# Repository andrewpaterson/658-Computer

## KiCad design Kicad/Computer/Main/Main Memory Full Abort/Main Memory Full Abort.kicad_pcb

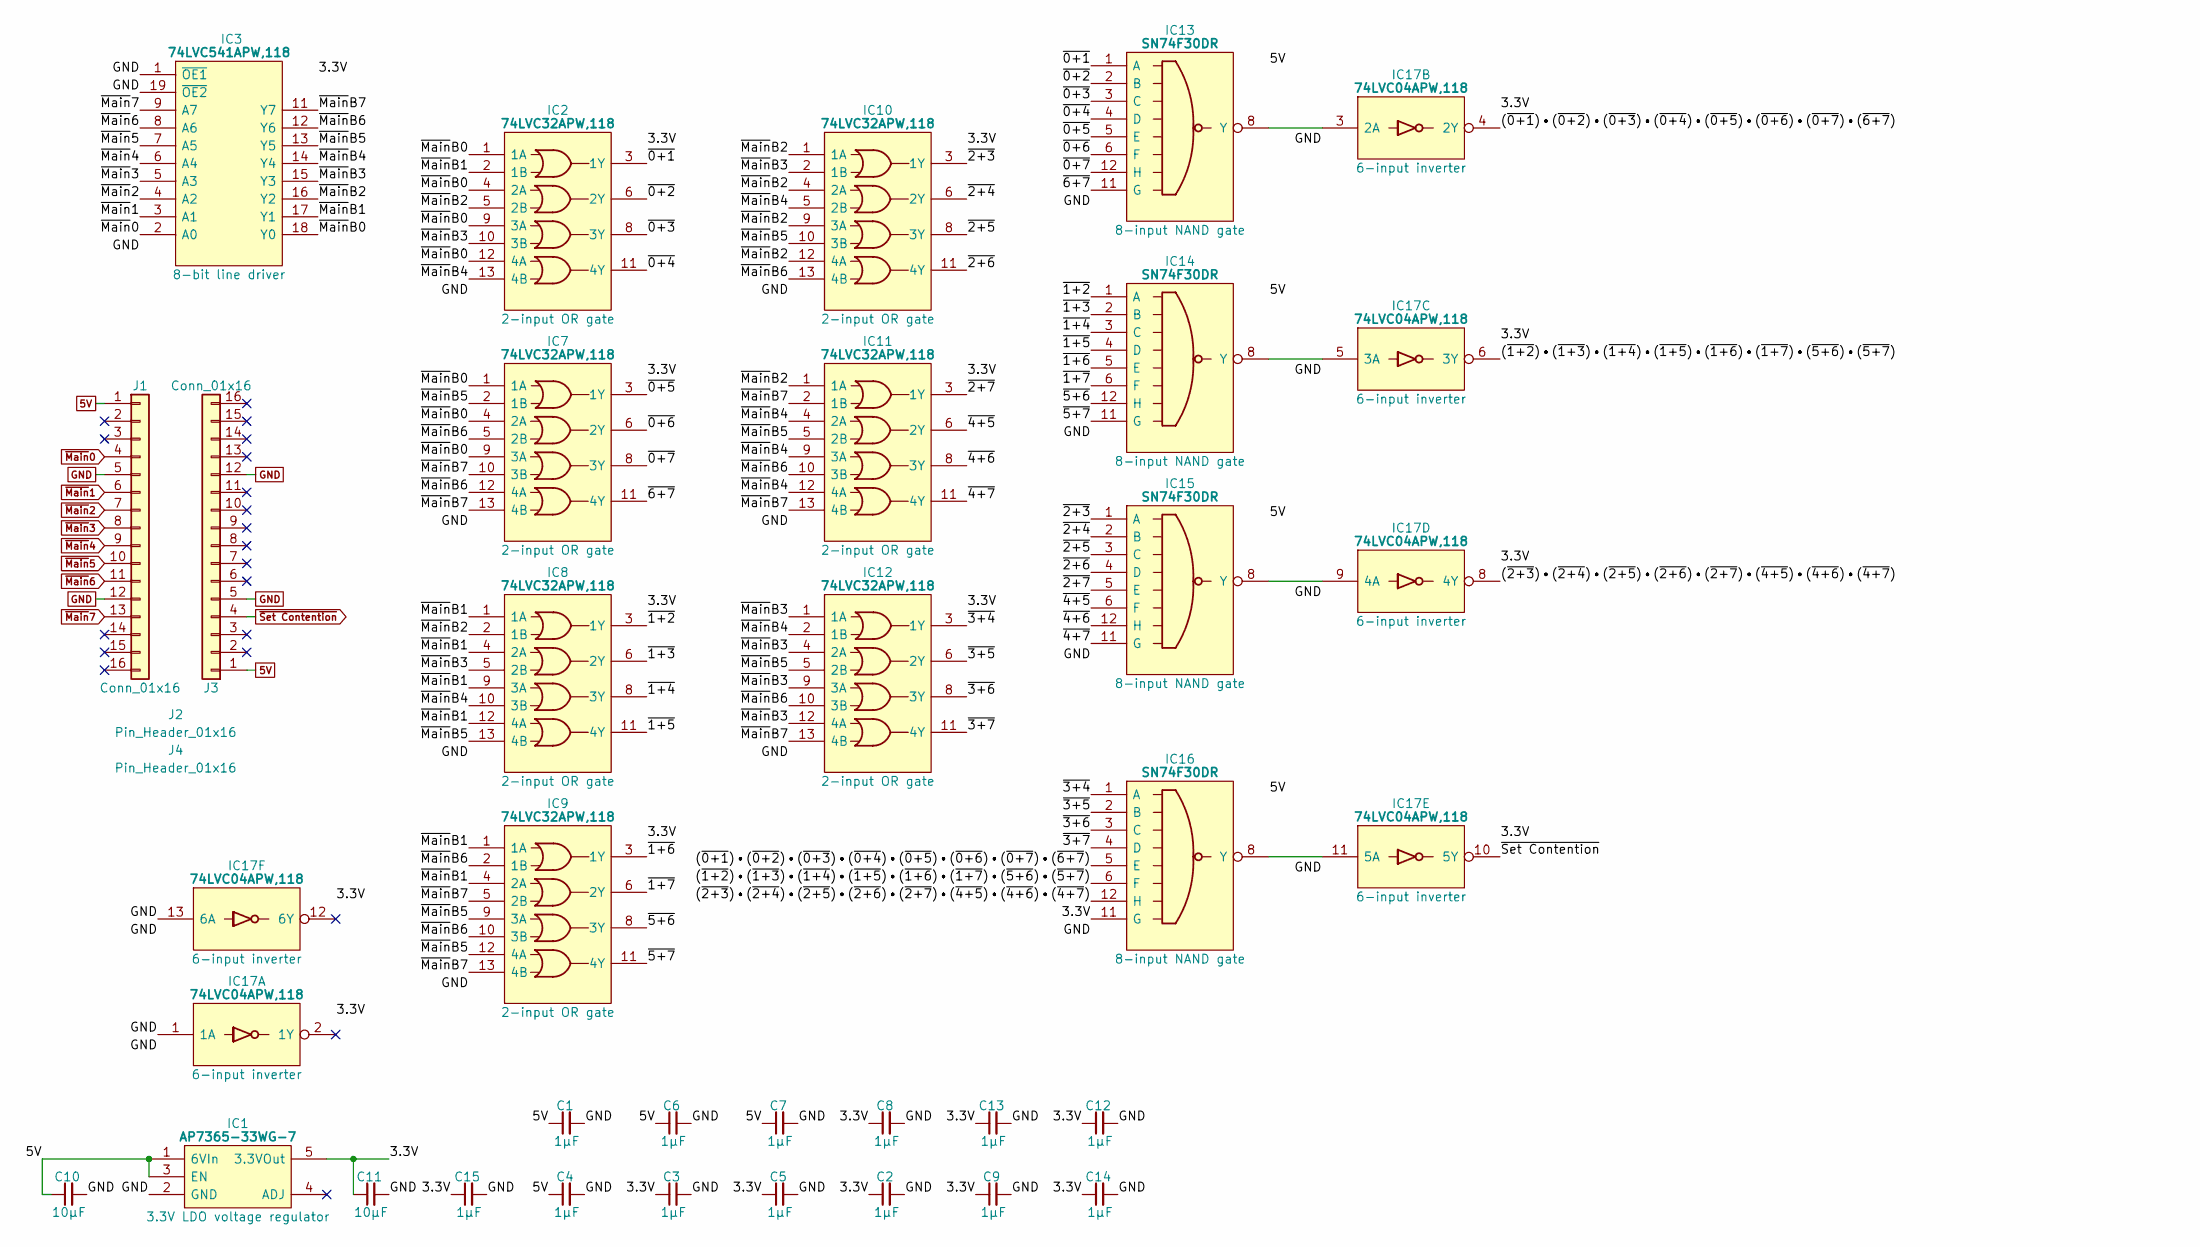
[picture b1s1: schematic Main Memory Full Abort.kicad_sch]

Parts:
C1, C2, C3, C4, C5, C6, C7, C8, C9, C12, C13, C14, C15: 1μF; C_0805
C10, C11: 10µF; C_0805
IC1: AP7365-33WG-7; SOT95P285X130-5N; Manufacturer_Part_Number AP7365-33WG-7; Mouser Part Number 621-AP7365-33WG-7
IC2, IC7, IC8, IC9, IC10, IC11, IC12: 74LVC32APW,118; SOP65P640X110-14N; Manufacturer_Part_Number 74LVC32APW,118; Mouser Part Number 771-74LVC32APW-T
IC3: 74LVC541APW,118; SOP65P640X110-20N; Mouser Part Number 771-74LVC541APW-T
IC13, IC14, IC15, IC16: SN74F30DR; SOIC127P600X175-14N; Manufacturer_Part_Number SN74F30DR; Mouser Part Number 595-SN74F30DR
IC17: 74LVC04APW,118; SOP65P640X110-14N; Manufacturer_Part_Number 74LVC04APW,118; Mouser Part Number 771-74LVC04APW-T
J1, J3: Conn_01x16; SIP_16_Pins
J2, J4: Pin_Header_01x16; PinHeader_1x16_P2.54mm_Vertical

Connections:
5V: C1.1, C4.1, C6.1, C7.1, C10.1, IC1.1 (6VIn), IC1.3 (EN), IC13.14 (5V), IC14.14 (5V), IC15.14 (5V), IC16.14 (5V), J1.1, J3.1
/3.3V: C2.1, C3.1, C5.1, C8.1, C9.1, C11.1, C12.1, C13.1, C14.1, C15.1, IC1.5 (3.3VOut), IC2.14 (3V), IC3.20 (3V), IC7.14 (3V), IC8.14 (3V), IC9.14 (3V), IC10.14 (3V), IC11.14 (3V), IC12.14 (3V), IC16.11 (G), IC17.14 (3V)
/(~0+1)•(~0+2)•(~0+3)•(~0+4)•(~0+5)•(~0+6)•(~0+7)•(~6+7): IC16.5 (E), IC17.4 (2Y)
/(~1+2)•(~1+3)•(~1+4)•(~1+5)•(~1+6)•(~1+7)•(~5+6)•(~5+7): IC16.6 (F), IC17.6 (3Y)
/(~2+3)•(~2+4)•(~2+5)•(~2+6)•(~2+7)•(~4+5)•(~4+6)•(~4+7): IC16.12 (H), IC17.8 (4Y)
/~0+1: IC2.3 (1Y), IC13.1 (A)
/~0+2: IC2.6 (2Y), IC13.2 (B)
/~0+3: IC2.8 (3Y), IC13.3 (C)
/~0+4: IC2.11 (4Y), IC13.4 (D)
/~0+5: IC7.3 (1Y), IC13.5 (E)
/~0+6: IC7.6 (2Y), IC13.6 (F)
/~0+7: IC7.8 (3Y), IC13.12 (H)
/~1+2: IC8.3 (1Y), IC14.1 (A)
/~1+3: IC8.6 (2Y), IC14.2 (B)
/~1+4: IC8.8 (3Y), IC14.3 (C)
/~1+5: IC8.11 (4Y), IC14.4 (D)
/~1+6: IC9.3 (1Y), IC14.5 (E)
/~1+7: IC9.6 (2Y), IC14.6 (F)
/~2+3: IC10.3 (1Y), IC15.1 (A)
/~2+4: IC10.6 (2Y), IC15.2 (B)
/~2+5: IC10.8 (3Y), IC15.3 (C)
/~2+6: IC10.11 (4Y), IC15.4 (D)
/~2+7: IC11.3 (1Y), IC15.5 (E)
/~3+4: IC12.3 (1Y), IC16.1 (A)
/~3+5: IC12.6 (2Y), IC16.2 (B)
/~3+6: IC12.8 (3Y), IC16.3 (C)
/~3+7: IC12.11 (4Y), IC16.4 (D)
/~4+5: IC11.6 (2Y), IC15.6 (F)
/~4+6: IC11.8 (3Y), IC15.12 (H)
/~4+7: IC11.11 (4Y), IC15.11 (G)
/~5+6: IC9.8 (3Y), IC14.12 (H)
/~5+7: IC9.11 (4Y), IC14.11 (G)
/~6+7: IC7.11 (4Y), IC13.11 (G)
/~MainB0: IC2.1 (1A), IC2.4 (2A), IC2.9 (3A), IC2.12 (4A), IC3.18 (Y0), IC7.1 (1A), IC7.4 (2A), IC7.9 (3A)
/~MainB1: IC2.2 (1B), IC3.17 (Y1), IC8.1 (1A), IC8.4 (2A), IC8.9 (3A), IC8.12 (4A), IC9.1 (1A), IC9.4 (2A)
/~MainB2: IC2.5 (2B), IC3.16 (Y2), IC8.2 (1B), IC10.1 (1A), IC10.4 (2A), IC10.9 (3A), IC10.12 (4A), IC11.1 (1A)
/~MainB3: IC2.10 (3B), IC3.15 (Y3), IC8.5 (2B), IC10.2 (1B), IC12.1 (1A), IC12.4 (2A), IC12.9 (3A), IC12.12 (4A)
/~MainB4: IC2.13 (4B), IC3.14 (Y4), IC8.10 (3B), IC10.5 (2B), IC11.4 (2A), IC11.9 (3A), IC11.12 (4A), IC12.2 (1B)
/~MainB5: IC3.13 (Y5), IC7.2 (1B), IC8.13 (4B), IC9.9 (3A), IC9.12 (4A), IC10.10 (3B), IC11.5 (2B), IC12.5 (2B)
/~MainB6: IC3.12 (Y6), IC7.5 (2B), IC7.12 (4A), IC9.2 (1B), IC9.10 (3B), IC10.13 (4B), IC11.10 (3B), IC12.10 (3B)
/~MainB7: IC3.11 (Y7), IC7.10 (3B), IC7.13 (4B), IC9.5 (2B), IC9.13 (4B), IC11.2 (1B), IC11.13 (4B), IC12.13 (4B)
GND: C1.2, C2.2, C3.2, C4.2, C5.2, C6.2, C7.2, C8.2, C9.2, C10.2, C11.2, C12.2, C13.2, C14.2, C15.2, IC1.2 (GND), IC2.7 (GND), IC3.1 (~OE1), IC3.10 (GND), IC3.19 (~OE2), IC7.7 (GND), IC8.7 (GND), IC9.7 (GND), IC10.7 (GND), IC11.7 (GND), IC12.7 (GND), IC13.7 (GND), IC14.7 (GND), IC15.7 (GND), IC16.7 (GND), IC17.1 (1A), IC17.7 (GND), IC17.13 (6A), J1.5, J1.12, J3.5, J3.12
unnamed: IC13.8 (Y), IC17.3 (2A)
unnamed: IC14.8 (Y), IC17.5 (3A)
unnamed: IC15.8 (Y), IC17.9 (4A)
unnamed: IC16.8 (Y), IC17.11 (5A)
~Main0: IC3.2 (A0), J1.4
~Main1: IC3.3 (A1), J1.6
~Main2: IC3.4 (A2), J1.7
~Main3: IC3.5 (A3), J1.8
~Main4: IC3.6 (A4), J1.9
~Main5: IC3.7 (A5), J1.10
~Main6: IC3.8 (A6), J1.11
~Main7: IC3.9 (A7), J1.13
~Set Contention: IC17.10 (5Y), J3.4

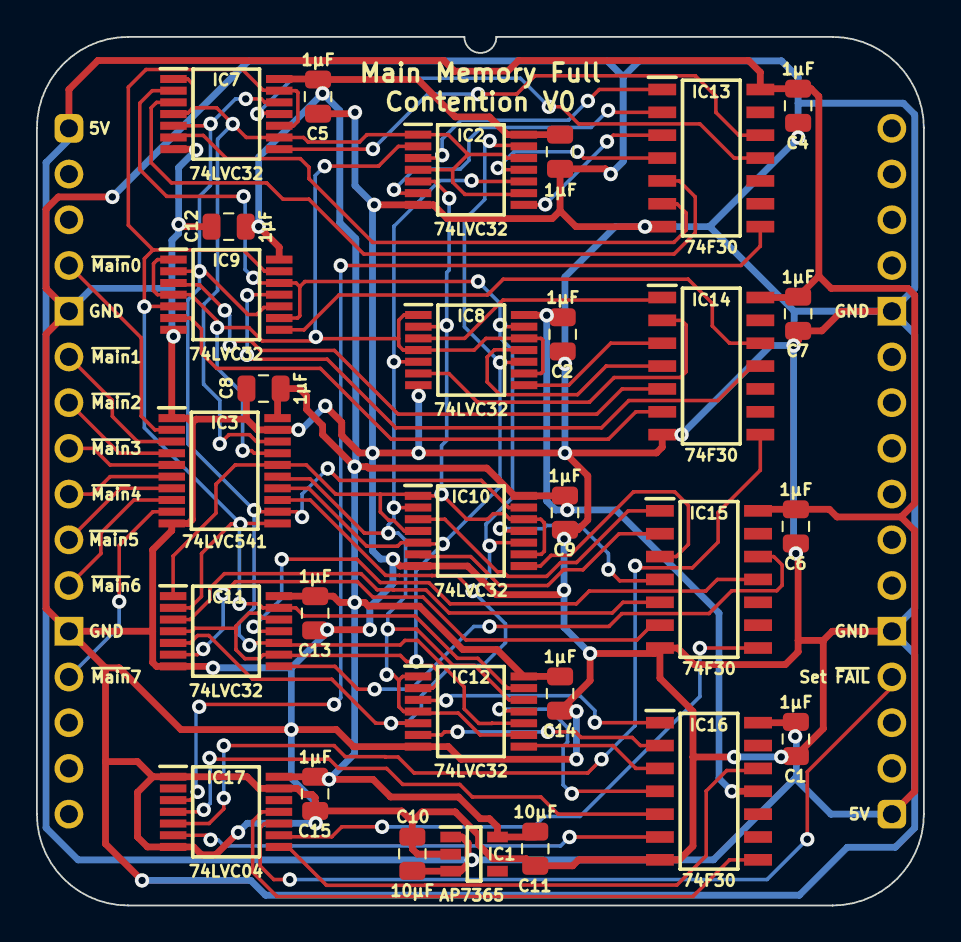
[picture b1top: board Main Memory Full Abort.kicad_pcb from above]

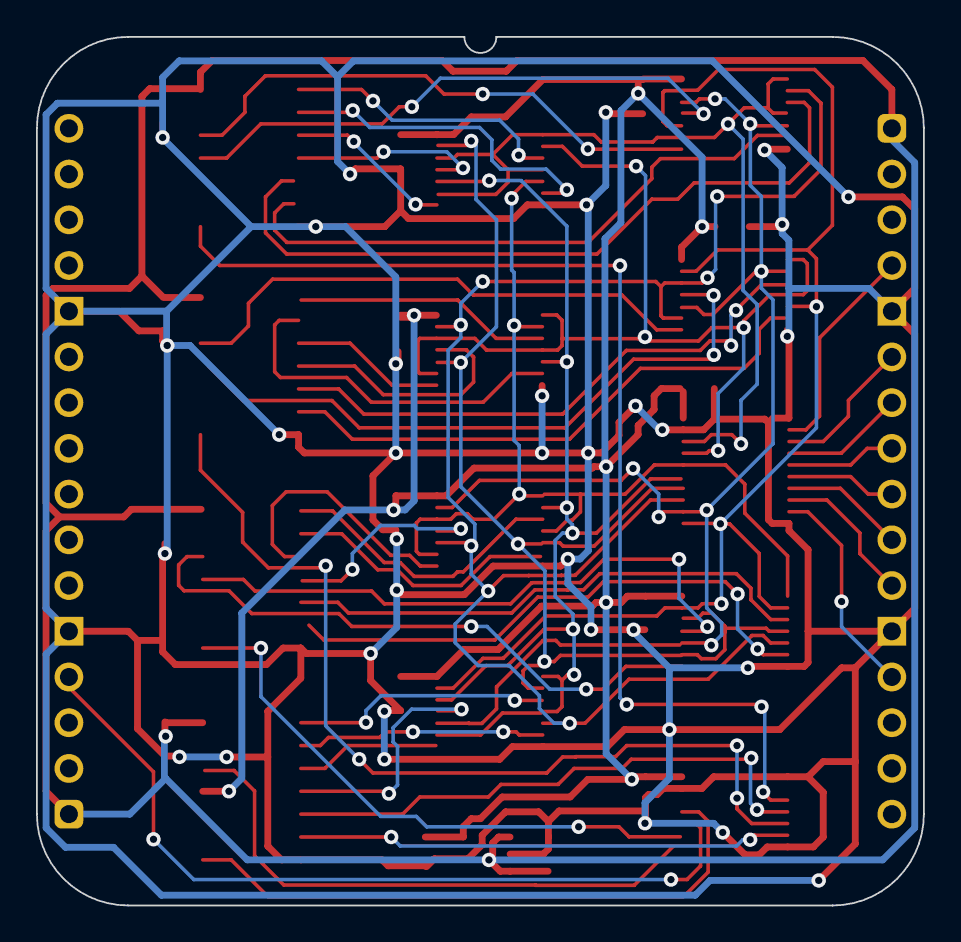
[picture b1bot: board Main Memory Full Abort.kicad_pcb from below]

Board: 2 copper layers, 49.3 x 48.3 mm, 33 parts (2 on the bottom side), 55 nets.

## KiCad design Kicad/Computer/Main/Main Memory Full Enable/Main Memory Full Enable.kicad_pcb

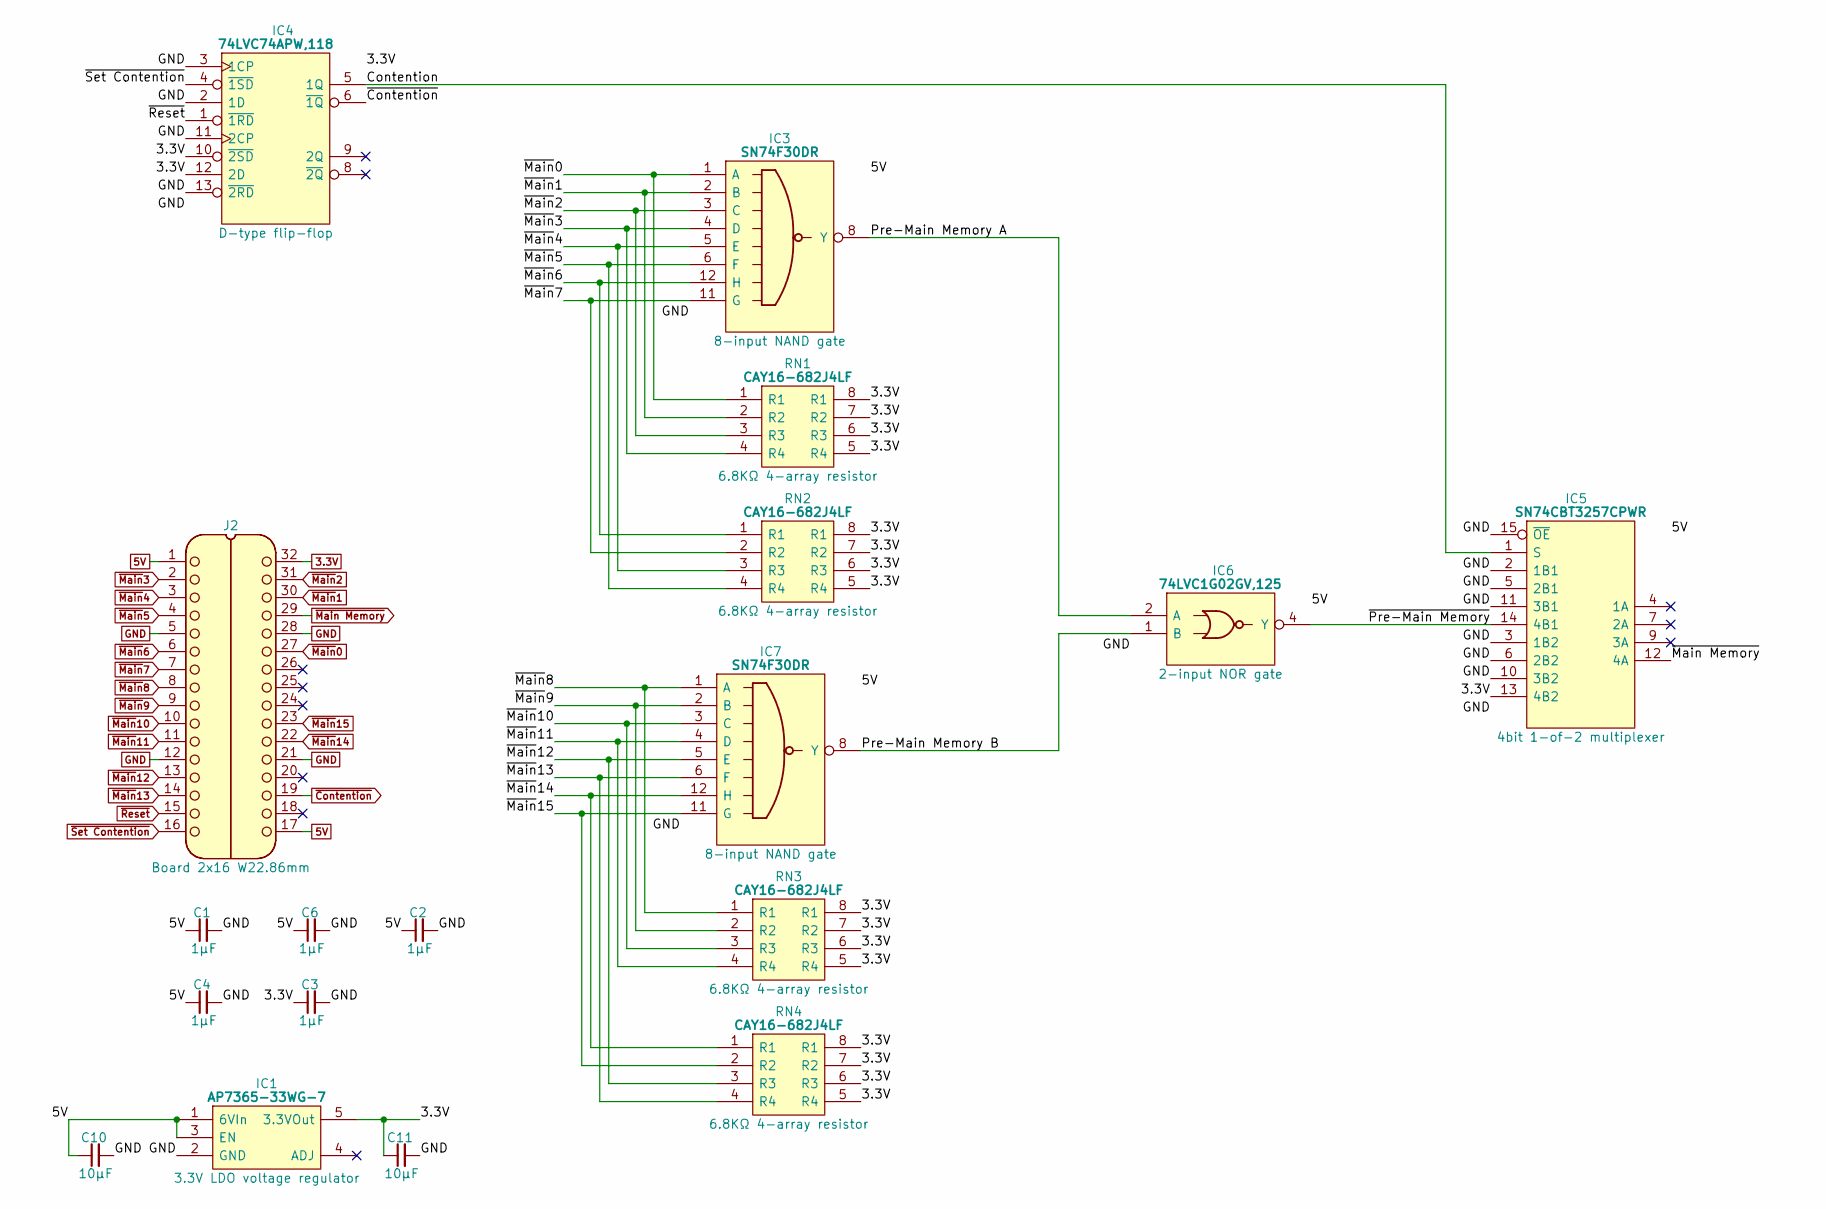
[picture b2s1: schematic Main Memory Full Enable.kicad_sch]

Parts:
C1, C2, C3, C4, C6: 1μF; C_0805
C10, C11: 10µF; C_0805
IC1: AP7365-33WG-7; SOT95P285X130-5N; Manufacturer_Part_Number AP7365-33WG-7; Mouser Part Number 621-AP7365-33WG-7
IC3, IC7: SN74F30DR; SOIC127P600X175-14N; Manufacturer_Part_Number SN74F30DR; Mouser Part Number 595-SN74F30DR
IC4: 74LVC74APW,118; SOP65P640X110-14N; Mouser Part Number 771-74LVC74APW-T
IC5: SN74CBT3257CPWR; SOP65P640X120-16N; Manufacturer_Part_Number SN74CBT3257CPWR; Mouser Part Number 595-SN74CBT3257CPWR
IC6: 74LVC1G02GV,125; SOT95P275X110-5N; Manufacturer_Part_Number 74LVC1G02GV,125; Mouser Part Number 771-LVC1G02GV125
J2: Board 2x16 W22.86mm; DIP-32_Board_W22.86mm
RN1, RN2, RN3, RN4: CAY16-682J4LF; CAY16-J4

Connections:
3.3V: C3.1, C11.1, IC1.5 (3.3VOut), IC4.10 (~2SD), IC4.12 (2D), IC4.14 (3V), IC5.13 (4B2), J2.32, RN1.5 (R4), RN1.6 (R3), RN1.7 (R2), RN1.8 (R1), RN2.5 (R4), RN2.6 (R3), RN2.7 (R2), RN2.8 (R1), RN3.5 (R4), RN3.6 (R3), RN3.7 (R2), RN3.8 (R1), RN4.5 (R4), RN4.6 (R3), RN4.7 (R2), RN4.8 (R1)
5V: C1.1, C2.1, C4.1, C6.1, C10.1, IC1.1 (6VIn), IC1.3 (EN), IC3.14 (5V), IC5.16 (5V), IC6.5 (3V), IC7.14 (5V), J2.1, J2.17
/Contention: IC4.5 (1Q), IC5.1 (S)
/Pre-Main Memory A: IC3.8 (Y), IC6.2 (A)
/Pre-Main Memory B: IC6.1 (B), IC7.8 (Y)
/~Pre-Main Memory: IC5.14 (4B1), IC6.4 (Y)
GND: C1.2, C2.2, C3.2, C4.2, C6.2, C10.2, C11.2, IC1.2 (GND), IC3.7 (GND), IC4.2 (1D), IC4.3 (1CP), IC4.7 (GND), IC4.11 (2CP), IC4.13 (~2RD), IC5.2 (1B1), IC5.3 (1B2), IC5.5 (2B1), IC5.6 (2B2), IC5.8 (GND), IC5.10 (3B2), IC5.11 (3B1), IC5.15 (~OE), IC6.3 (GND), IC7.7 (GND), J2.5, J2.12, J2.21, J2.28
~Contention: IC4.6 (~1Q), J2.19
~Main Memory: IC5.12 (4A), J2.29
~Main0: IC3.1 (A), J2.27, RN1.1 (R1)
~Main1: IC3.2 (B), J2.30, RN1.2 (R2)
~Main2: IC3.3 (C), J2.31, RN1.3 (R3)
~Main3: IC3.4 (D), J2.2, RN1.4 (R4)
~Main4: IC3.5 (E), J2.3, RN2.3 (R3)
~Main5: IC3.6 (F), J2.4, RN2.4 (R4)
~Main6: IC3.12 (H), J2.6, RN2.1 (R1)
~Main7: IC3.11 (G), J2.7, RN2.2 (R2)
~Main8: IC7.1 (A), J2.8, RN3.1 (R1)
~Main9: IC7.2 (B), J2.9, RN3.2 (R2)
~Main10: IC7.3 (C), J2.10, RN3.3 (R3)
~Main11: IC7.4 (D), J2.11, RN3.4 (R4)
~Main12: IC7.5 (E), J2.13, RN4.3 (R3)
~Main13: IC7.6 (F), J2.14, RN4.4 (R4)
~Main14: IC7.12 (H), J2.22, RN4.1 (R1)
~Main15: IC7.11 (G), J2.23, RN4.2 (R2)
~Reset: IC4.1 (~1RD), J2.15
~Set Contention: IC4.4 (~1SD), J2.16

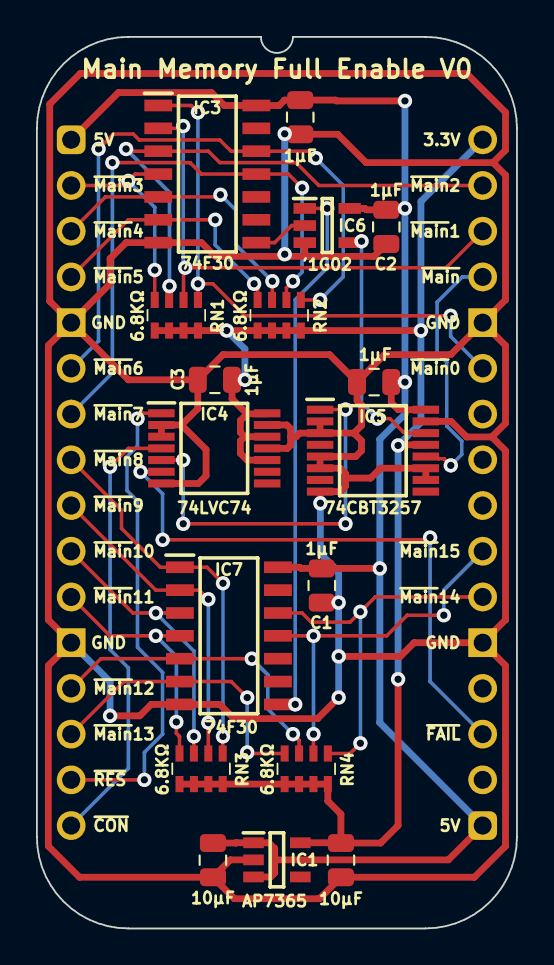
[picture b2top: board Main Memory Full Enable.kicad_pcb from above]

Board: 2 copper layers, 26.7 x 49.5 mm, 18 parts (0 on the bottom side), 27 nets.

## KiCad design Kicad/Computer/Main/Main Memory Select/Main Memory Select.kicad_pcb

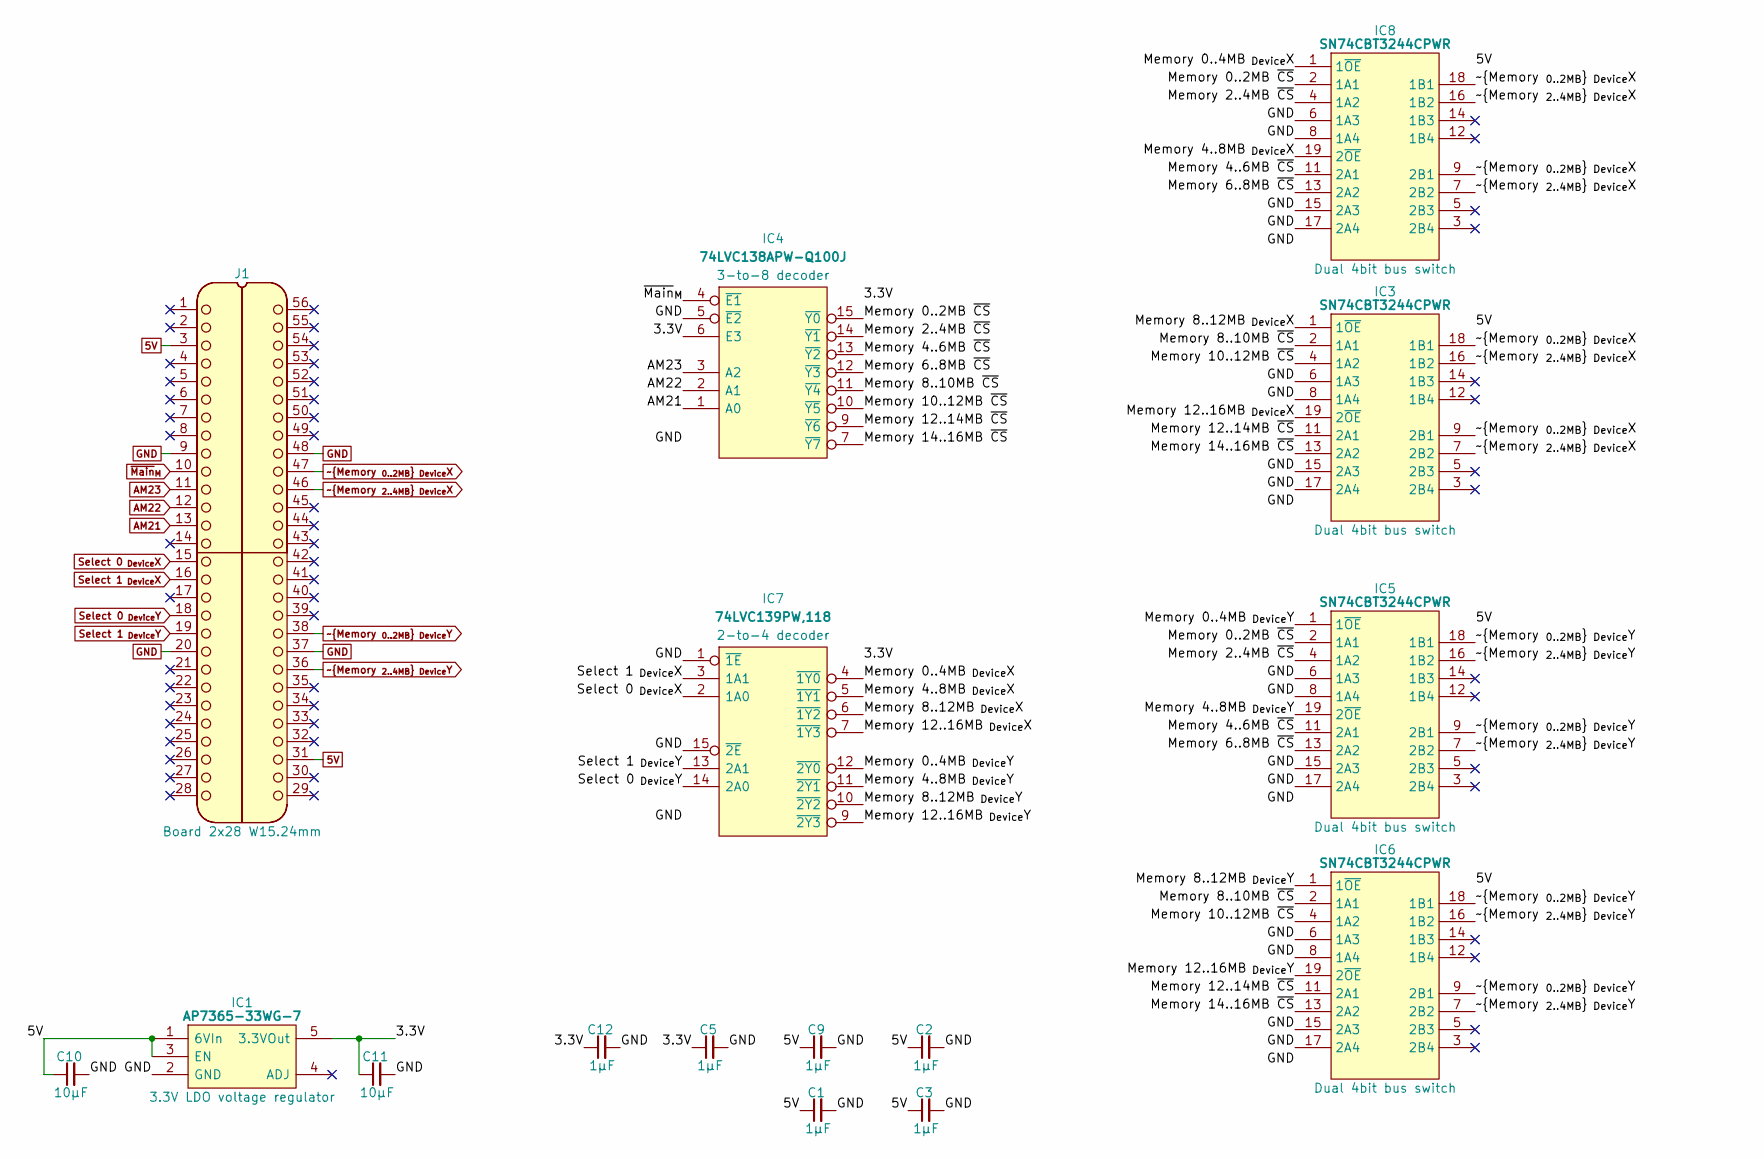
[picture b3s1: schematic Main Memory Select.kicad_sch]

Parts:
C1, C2, C3, C5, C9, C12: 1μF; C_0805
C10, C11: 10µF; C_0805
IC1: AP7365-33WG-7; SOT95P285X130-5N; Manufacturer_Part_Number AP7365-33WG-7; Mouser Part Number 621-AP7365-33WG-7
IC3, IC5, IC6, IC8: SN74CBT3244CPWR; SOP65P640X120-20N; Manufacturer_Part_Number SN74CBT3244CPWR; Mouser Part Number 595-SN74CBT3244CPWR
IC4: 74LVC138APW-Q100J; SOP65P640X110-16N; Mouser Part Number 771-74LVC138APWQ100J
IC7: 74LVC139PW,118; SOP65P640X110-16N; Mouser Part Number 771-74LVC139PW-T
J1: Board 2x28 W15.24mm; DIP-56_Board_W15.24mm

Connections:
5V: C1.1, C2.1, C3.1, C9.1, C10.1, IC1.1 (6VIn), IC1.3 (EN), IC3.20 (5V), IC5.20 (5V), IC6.20 (5V), IC8.20 (5V), J1.3, J1.31
/3.3V: C5.1, C11.1, C12.1, IC1.5 (3.3VOut), IC4.6 (E3), IC4.16 (3V), IC7.16 (3V)
/Memory 0..2MB ~CS: IC4.15 (~Y0), IC5.2 (1A1), IC8.2 (1A1)
/Memory 0..4MB_{ Device}X: IC7.4 (~1Y0), IC8.1 (1~OE)
/Memory 0..4MB_{ Device}Y: IC5.1 (1~OE), IC7.12 (~2Y0)
/Memory 2..4MB ~CS: IC4.14 (~Y1), IC5.4 (1A2), IC8.4 (1A2)
/Memory 4..6MB ~CS: IC4.13 (~Y2), IC5.11 (2A1), IC8.11 (2A1)
/Memory 4..8MB_{ Device}X: IC7.5 (~1Y1), IC8.19 (2~OE)
/Memory 4..8MB_{ Device}Y: IC5.19 (2~OE), IC7.11 (~2Y1)
/Memory 6..8MB ~CS: IC4.12 (~Y3), IC5.13 (2A2), IC8.13 (2A2)
/Memory 8..10MB ~CS: IC3.2 (1A1), IC4.11 (~Y4), IC6.2 (1A1)
/Memory 8..12MB_{ Device}X: IC3.1 (1~OE), IC7.6 (~1Y2)
/Memory 8..12MB_{ Device}Y: IC6.1 (1~OE), IC7.10 (~2Y2)
/Memory 10..12MB ~CS: IC3.4 (1A2), IC4.10 (~Y5), IC6.4 (1A2)
/Memory 12..14MB ~CS: IC3.11 (2A1), IC4.9 (~Y6), IC6.11 (2A1)
/Memory 12..16MB_{ Device}X: IC3.19 (2~OE), IC7.7 (~1Y3)
/Memory 12..16MB_{ Device}Y: IC6.19 (2~OE), IC7.9 (~2Y3)
/Memory 14..16MB ~CS: IC3.13 (2A2), IC4.7 (~Y7), IC6.13 (2A2)
AM21: IC4.1 (A0), J1.13
AM22: IC4.2 (A1), J1.12
AM23: IC4.3 (A2), J1.11
GND: C1.2, C2.2, C3.2, C5.2, C9.2, C10.2, C11.2, C12.2, IC1.2 (GND), IC3.6 (1A3), IC3.8 (1A4), IC3.10 (GND), IC3.15 (2A3), IC3.17 (2A4), IC4.5 (~E2), IC4.8 (GND), IC5.6 (1A3), IC5.8 (1A4), IC5.10 (GND), IC5.15 (2A3), IC5.17 (2A4), IC6.6 (1A3), IC6.8 (1A4), IC6.10 (GND), IC6.15 (2A3), IC6.17 (2A4), IC7.1 (~1E), IC7.8 (GND), IC7.15 (~2E), IC8.6 (1A3), IC8.8 (1A4), IC8.10 (GND), IC8.15 (2A3), IC8.17 (2A4), J1.9, J1.20, J1.37, J1.48
Select 0_{ Device}X: IC7.2 (1A0), J1.15
Select 0_{ Device}Y: IC7.14 (2A0), J1.18
Select 1_{ Device}X: IC7.3 (1A1), J1.16
Select 1_{ Device}Y: IC7.13 (2A1), J1.19
~Main_{M}: IC4.4 (~E1), J1.10
~Memory _{0..2MB}_{ Device}X: IC3.9 (2B1), IC3.18 (1B1), IC8.9 (2B1), IC8.18 (1B1), J1.47
~Memory _{0..2MB}_{ Device}Y: IC5.9 (2B1), IC5.18 (1B1), IC6.9 (2B1), IC6.18 (1B1), J1.38
~Memory _{2..4MB}_{ Device}X: IC3.7 (2B2), IC3.16 (1B2), IC8.7 (2B2), IC8.16 (1B2), J1.46
~Memory _{2..4MB}_{ Device}Y: IC5.7 (2B2), IC5.16 (1B2), IC6.7 (2B2), IC6.16 (1B2), J1.36

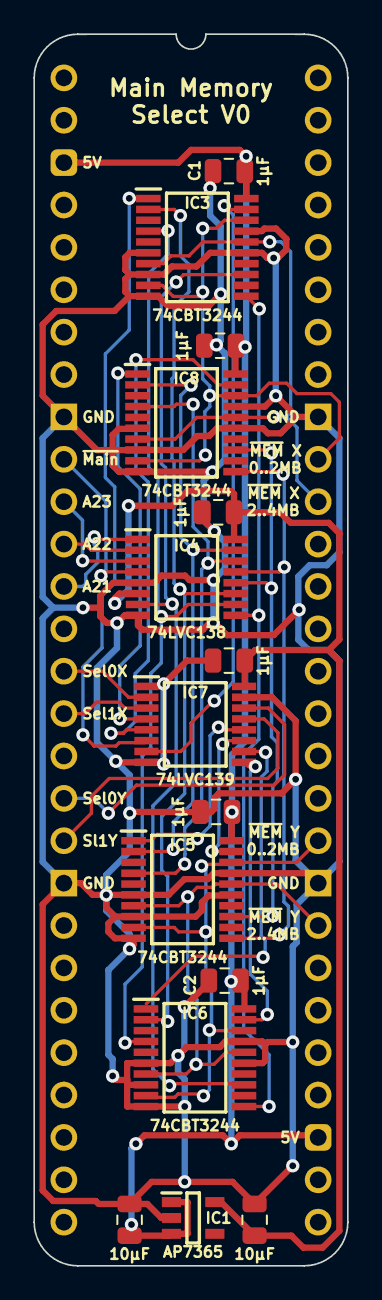
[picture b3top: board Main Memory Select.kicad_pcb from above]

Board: 2 copper layers, 18.8 x 73.8 mm, 16 parts (0 on the bottom side), 31 nets.

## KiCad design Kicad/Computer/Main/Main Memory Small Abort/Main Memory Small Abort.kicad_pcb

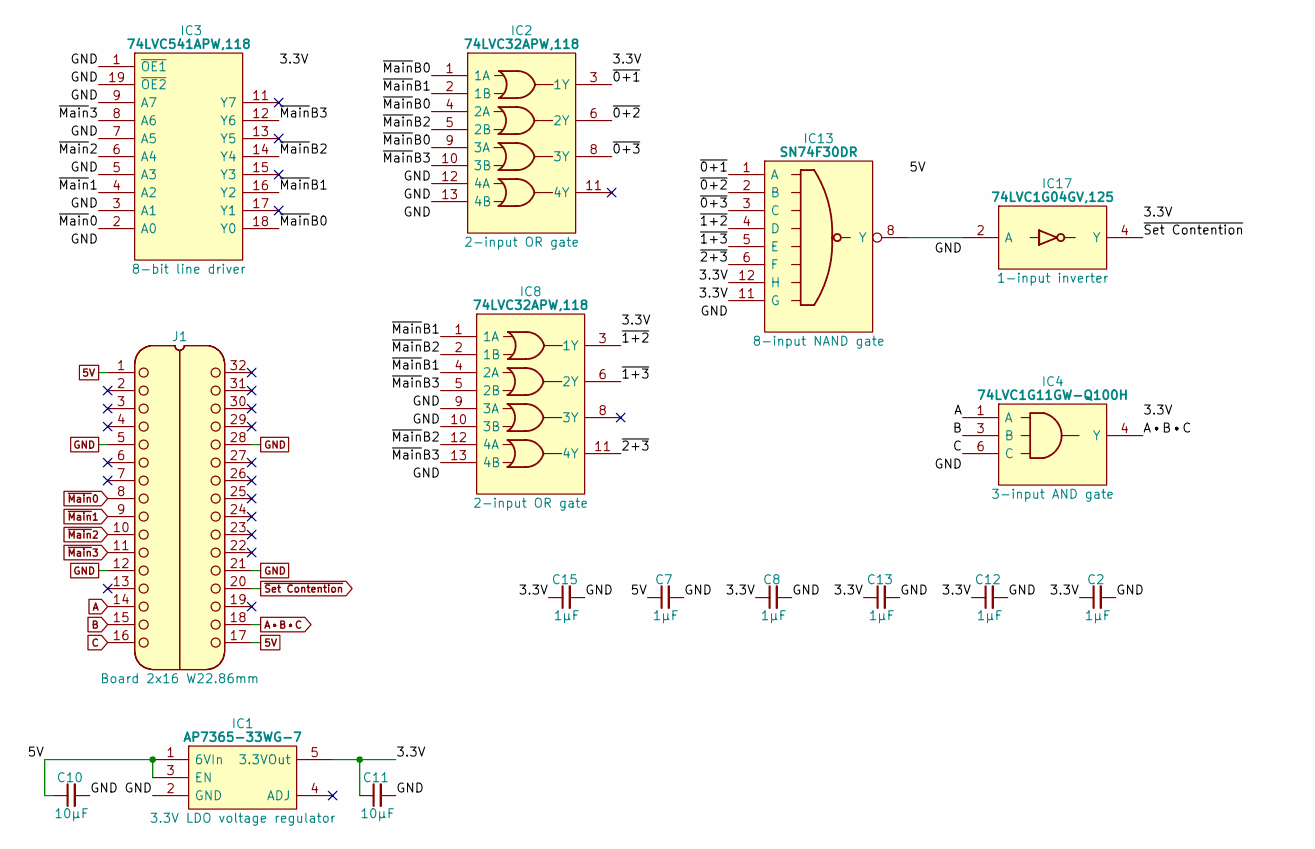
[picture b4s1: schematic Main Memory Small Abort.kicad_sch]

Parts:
C2, C7, C8, C12, C13, C15: 1μF; C_0805
C10, C11: 10µF; C_0805
IC1: AP7365-33WG-7; SOT95P285X130-5N; Manufacturer_Part_Number AP7365-33WG-7; Mouser Part Number 621-AP7365-33WG-7
IC2, IC8: 74LVC32APW,118; SOP65P640X110-14N; Manufacturer_Part_Number 74LVC32APW,118; Mouser Part Number 771-74LVC32APW-T
IC3: 74LVC541APW,118; SOP65P640X110-20N; Mouser Part Number 771-74LVC541APW-T
IC4: 74LVC1G11GW-Q100H; SOP65P210X110-6N; Manufacturer_Part_Number 74LVC1G11GW-Q100H; Mouser Part Number 771-74LVC1G11GWQ100H
IC13: SN74F30DR; SOIC127P600X175-14N; Manufacturer_Part_Number SN74F30DR; Mouser Part Number 595-SN74F30DR
IC17: 74LVC1G04GV,125; SOT95P275X110-5N; Manufacturer_Part_Number 74LVC1G04GV,125; Mouser Part Number 771-74LVC1G04GV
J1: Board 2x16 W22.86mm; DIP-32_Board_W22.86mm

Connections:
5V: C7.1, C10.1, IC1.1 (6VIn), IC1.3 (EN), IC13.14 (5V), J1.1, J1.17
/3.3V: C2.1, C8.1, C11.1, C12.1, C13.1, C15.1, IC1.5 (3.3VOut), IC2.14 (3V), IC3.20 (3V), IC4.5 (3V), IC8.14 (3V), IC13.11 (G), IC13.12 (H), IC17.5 (3V)
/~0+1: IC2.3 (1Y), IC13.1 (A)
/~0+2: IC2.6 (2Y), IC13.2 (B)
/~0+3: IC2.8 (3Y), IC13.3 (C)
/~1+2: IC8.3 (1Y), IC13.4 (D)
/~1+3: IC8.6 (2Y), IC13.5 (E)
/~2+3: IC8.11 (4Y), IC13.6 (F)
/~MainB0: IC2.1 (1A), IC2.4 (2A), IC2.9 (3A), IC3.18 (Y0)
/~MainB1: IC2.2 (1B), IC3.16 (Y2), IC8.1 (1A), IC8.4 (2A)
/~MainB2: IC2.5 (2B), IC3.14 (Y4), IC8.2 (1B), IC8.12 (4A)
/~MainB3: IC2.10 (3B), IC3.12 (Y6), IC8.5 (2B), IC8.13 (4B)
A: IC4.1 (A), J1.14
A•B•C: IC4.4 (Y), J1.18
B: IC4.3 (B), J1.15
C: IC4.6 (C), J1.16
GND: C2.2, C7.2, C8.2, C10.2, C11.2, C12.2, C13.2, C15.2, IC1.2 (GND), IC2.7 (GND), IC2.12 (4A), IC2.13 (4B), IC3.1 (~OE1), IC3.3 (A1), IC3.5 (A3), IC3.7 (A5), IC3.9 (A7), IC3.10 (GND), IC3.19 (~OE2), IC4.2 (GND), IC8.7 (GND), IC8.9 (3A), IC8.10 (3B), IC13.7 (GND), IC17.3 (GND), J1.5, J1.12, J1.21, J1.28
unnamed: IC13.8 (Y), IC17.2 (A)
~Main0: IC3.2 (A0), J1.8
~Main1: IC3.4 (A2), J1.9
~Main2: IC3.6 (A4), J1.10
~Main3: IC3.8 (A6), J1.11
~Set Contention: IC17.4 (Y), J1.20

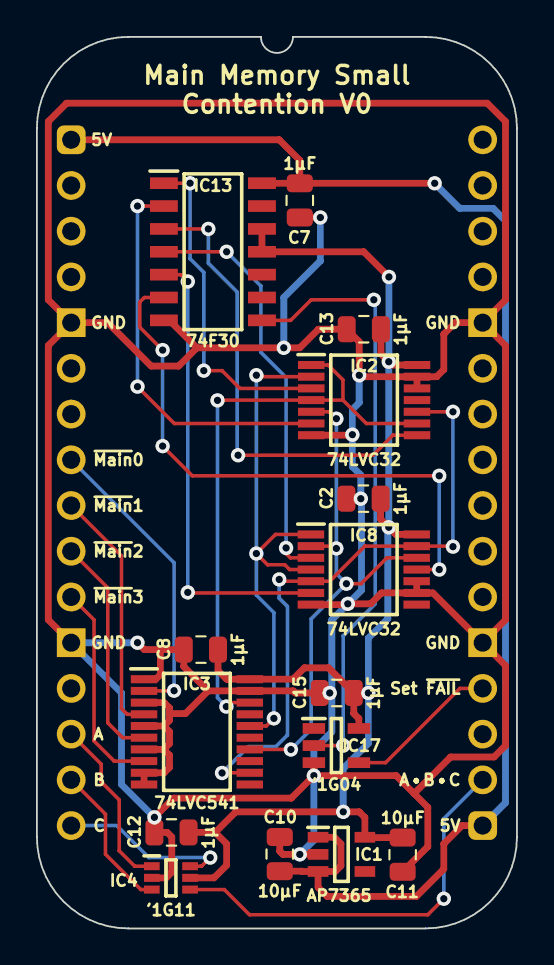
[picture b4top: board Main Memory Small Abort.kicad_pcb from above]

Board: 2 copper layers, 26.7 x 49.5 mm, 16 parts (0 on the bottom side), 23 nets.

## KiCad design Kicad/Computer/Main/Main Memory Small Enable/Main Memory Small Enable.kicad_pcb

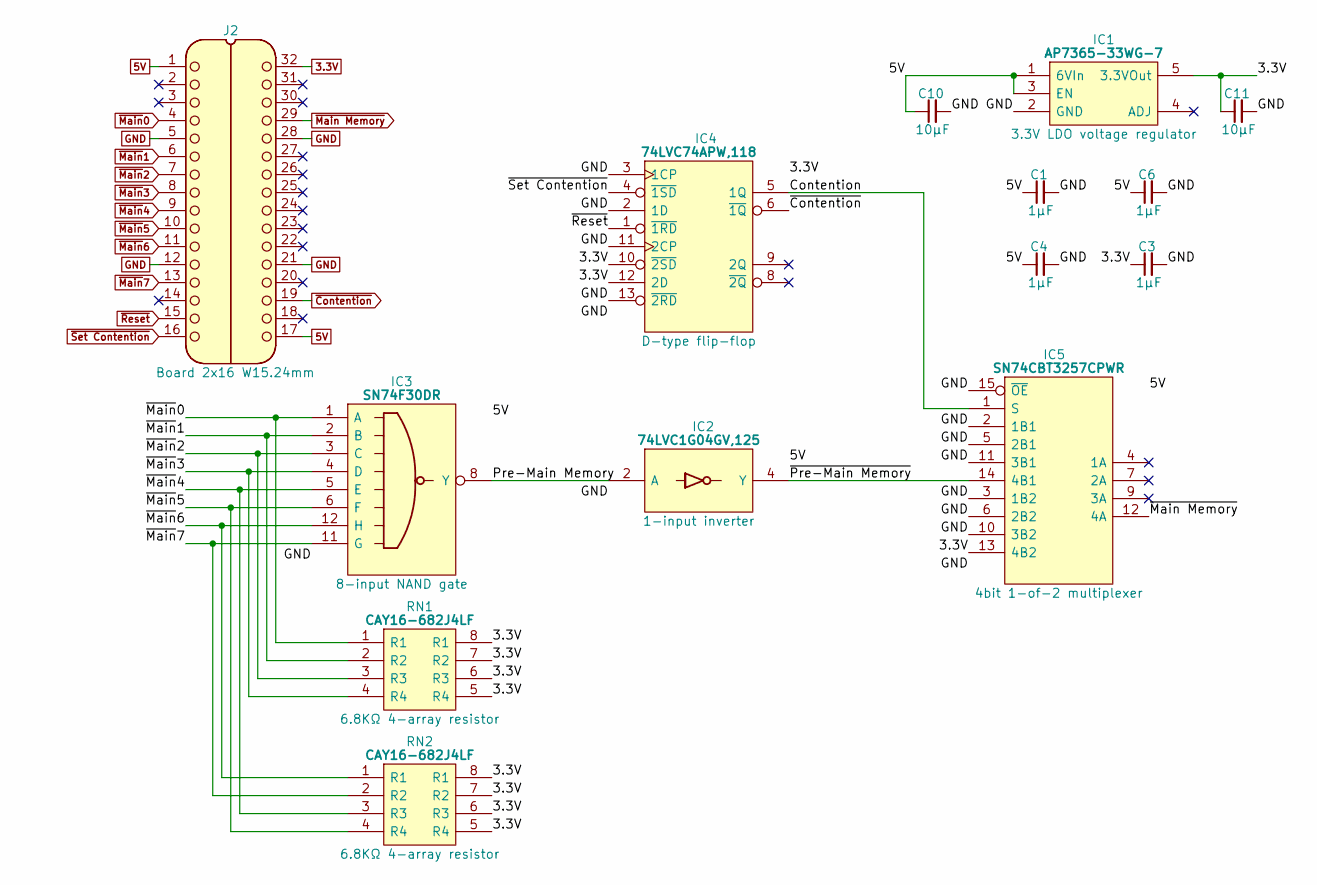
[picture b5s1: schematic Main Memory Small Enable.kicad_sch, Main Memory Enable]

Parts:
C1, C3, C4, C6: 1μF; C_0805
C10, C11: 10µF; C_0805
IC1: AP7365-33WG-7; SOT95P285X130-5N; Manufacturer_Part_Number AP7365-33WG-7; Mouser Part Number 621-AP7365-33WG-7
IC2: 74LVC1G04GV,125; SOT95P275X110-5N; Manufacturer_Part_Number 74LVC1G04GV,125; Mouser Part Number 771-74LVC1G04GV
IC3: SN74F30DR; SOIC127P600X175-14N; Manufacturer_Part_Number SN74F30DR; Mouser Part Number 595-SN74F30DR
IC4: 74LVC74APW,118; SOP65P640X110-14N; Mouser Part Number 771-74LVC74APW-T
IC5: SN74CBT3257CPWR; SOP65P640X120-16N; Manufacturer_Part_Number SN74CBT3257CPWR; Mouser Part Number 595-SN74CBT3257CPWR
J2: Board 2x16 W15.24mm; DIP-32_Board_W15.24mm
RN1, RN2: CAY16-682J4LF; CAY16-J4

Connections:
3.3V: C3.1, C11.1, IC1.5 (3.3VOut), IC4.10 (~2SD), IC4.12 (2D), IC4.14 (3V), IC5.13 (4B2), J2.32, RN1.5 (R4), RN1.6 (R3), RN1.7 (R2), RN1.8 (R1), RN2.5 (R4), RN2.6 (R3), RN2.7 (R2), RN2.8 (R1)
5V: C1.1, C4.1, C6.1, C10.1, IC1.1 (6VIn), IC1.3 (EN), IC2.5 (3V), IC3.14 (5V), IC5.16 (5V), J2.1, J2.17
/Contention: IC4.5 (1Q), IC5.1 (S)
/Pre-Main Memory: IC2.2 (A), IC3.8 (Y)
/~Pre-Main Memory: IC2.4 (Y), IC5.14 (4B1)
GND: C1.2, C3.2, C4.2, C6.2, C10.2, C11.2, IC1.2 (GND), IC2.3 (GND), IC3.7 (GND), IC4.2 (1D), IC4.3 (1CP), IC4.7 (GND), IC4.11 (2CP), IC4.13 (~2RD), IC5.2 (1B1), IC5.3 (1B2), IC5.5 (2B1), IC5.6 (2B2), IC5.8 (GND), IC5.10 (3B2), IC5.11 (3B1), IC5.15 (~OE), J2.5, J2.12, J2.21, J2.28
~Contention: IC4.6 (~1Q), J2.19
~Main Memory: IC5.12 (4A), J2.29
~Main0: IC3.1 (A), J2.4, RN1.1 (R1)
~Main1: IC3.2 (B), J2.6, RN1.2 (R2)
~Main2: IC3.3 (C), J2.7, RN1.3 (R3)
~Main3: IC3.4 (D), J2.8, RN1.4 (R4)
~Main4: IC3.5 (E), J2.9, RN2.3 (R3)
~Main5: IC3.6 (F), J2.10, RN2.4 (R4)
~Main6: IC3.12 (H), J2.11, RN2.1 (R1)
~Main7: IC3.11 (G), J2.13, RN2.2 (R2)
~Reset: IC4.1 (~1RD), J2.15
~Set Contention: IC4.4 (~1SD), J2.16

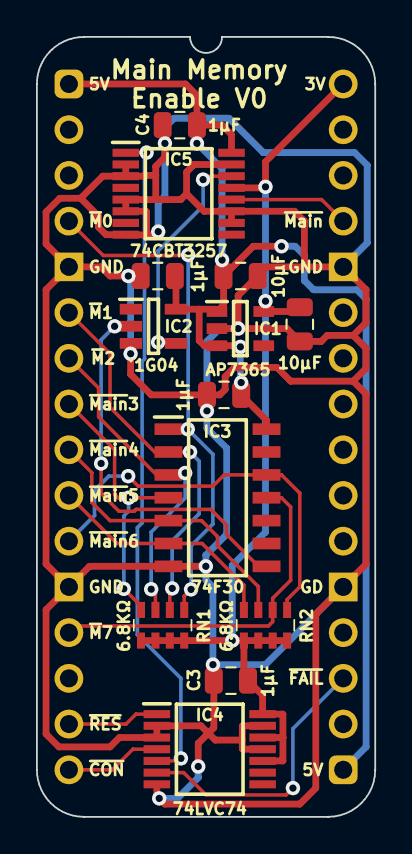
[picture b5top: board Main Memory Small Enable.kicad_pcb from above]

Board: 2 copper layers, 18.8 x 43.3 mm, 14 parts (0 on the bottom side), 18 nets.
